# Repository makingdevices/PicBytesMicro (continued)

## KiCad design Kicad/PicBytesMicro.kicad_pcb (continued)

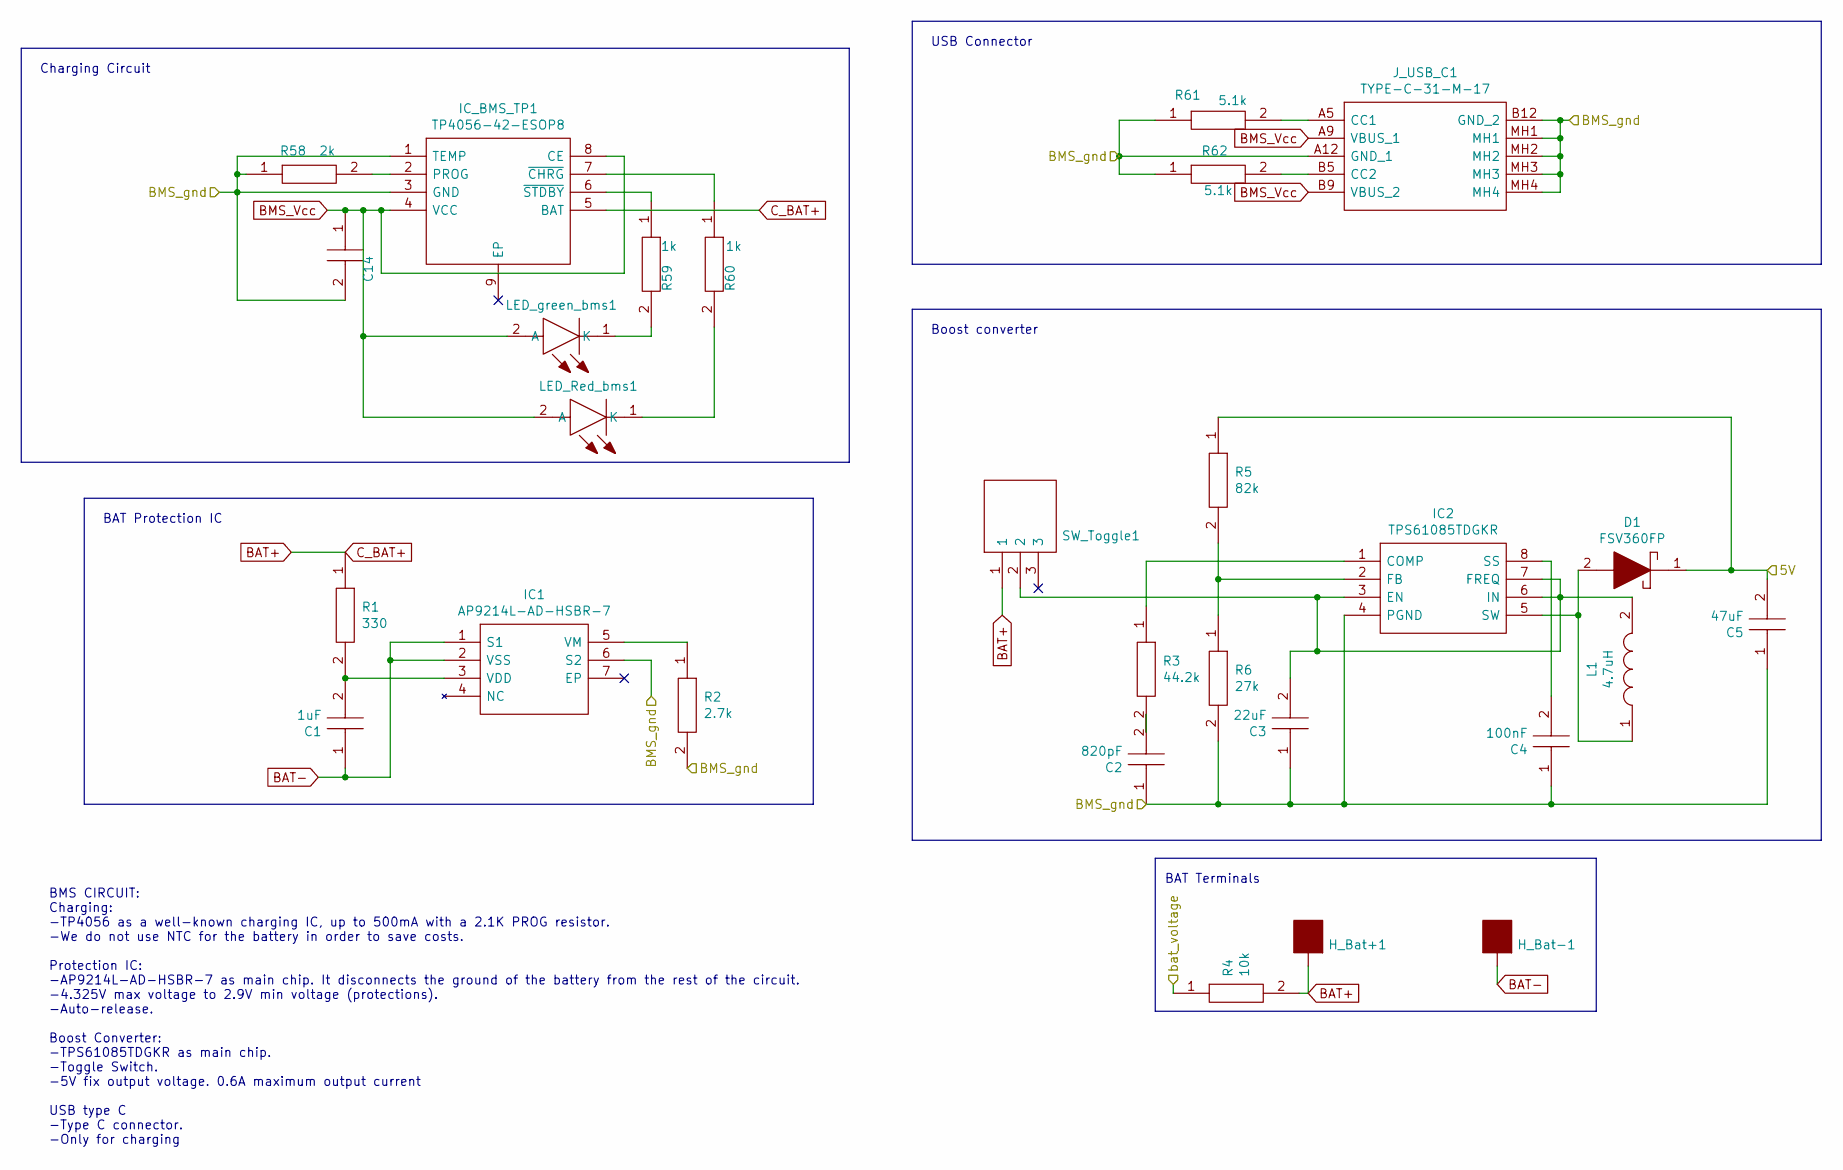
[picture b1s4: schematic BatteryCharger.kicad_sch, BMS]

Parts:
C1: 1uF; CAPC2012X140N; Manufacturer_Part_Number C0805C475M8RACTU
C2: 820pF; CAPC2012X140N; Manufacturer_Part_Number C0805C475M8RACTU
C3: 22uF; CAPC2012X140N; Manufacturer_Part_Number C0805C475M8RACTU
C4: 100nF; CAPC2012X140N; Manufacturer_Part_Number C0805C475M8RACTU
C5: 47uF; CAPC2012X140N; Manufacturer_Part_Number C0805C475M8RACTU
C14: 10uF; CAPC2012X145N; Manufacturer_Part_Number GCG21BR71H154KA01K
D1: FSV360FP; SS12FP; Mouser Part Number 512-FSV360FP
H_Bat+1: MountingHole_Pad-User_library-SamacSys_Parts; Mounting-Pad
H_Bat-1: MountingHole_Pad-User_library-SamacSys_Parts; Mounting-Pad
IC1: AP9214L-AD-HSBR-7; AP9214LANHSBR7; Mouser Part Number 621-AP9214L-AN-HSBR7
IC2: TPS61085TDGKR; SOP65P490X110-8N; Mouser Part Number 595-TPS61085TDGKR
IC_BMS_TP1: TP4056-42-ESOP8; SOIC127P600X175-9N; Manufacturer_Part_Number TP4056-42-ESOP8
J_USB_C1: TYPE-C-31-M-17; TYPEC31M17; Manufacturer_Part_Number TYPE-C-31-M-17
L1: 4.7uH; SRN6045_1; Mouser Part Number 652-SRN6045-4R7Y
LED_Red_bms1: LTST-C171GKT; LEDC2012X90N; Manufacturer_Part_Number LTST-C171GKT
LED_green_bms1: LTST-C171GKT; LEDC2012X90N; Manufacturer_Part_Number LTST-C171GKT
R1: 330; RESC2012X75N; Manufacturer_Part_Number ERJP6WF1303V
R2: 2.7k; RESC2012X75N; Manufacturer_Part_Number ERJP6WF1303V
R3: 44.2k; RESC2012X75N; Manufacturer_Part_Number ERJP6WF1303V
R4: 10k; RESC2012X75N; Manufacturer_Part_Number ERJP6WF1303V
R5: 82k; RESC2012X75N; Manufacturer_Part_Number ERJP6WF1303V
R6: 27k; RESC2012X75N; Manufacturer_Part_Number ERJP6WF1303V
R58: 2k; RESC2012X65N; Manufacturer_Part_Number KTR10EZPF4220
R59, R60: 1k; RESC2012X65N; Manufacturer_Part_Number KTR10EZPF4220
R61, R62: 5.1k; RESC2012X65N; Manufacturer_Part_Number KTR10EZPF4220
SW_Toggle1: K3-1260D-L1; K31260DL1; Manufacturer_Part_Number K3-1260D-L1

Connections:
BAT+: H_Bat+1.1, IC_BMS_TP1.5 (BAT), R1.1, R4.2, SW_Toggle1.1
BAT-: C1.1, H_Bat-1.1, IC1.1 (S1), IC1.2 (VSS)
BMS_Vcc: C14.1, IC_BMS_TP1.4 (VCC), IC_BMS_TP1.8 (CE), J_USB_C1.A9 (VBUS_1), J_USB_C1.B9 (VBUS_2), LED_Red_bms1.2 (A), LED_green_bms1.2 (A)
unnamed: C2.2, R3.2
unnamed: C1.2, IC1.3 (VDD), R1.2
unnamed: IC1.5 (VM), R2.1
unnamed: IC2.1 (COMP), R3.1
unnamed: C3.2, IC2.3 (EN), IC2.6 (IN), IC2.7 (FREQ), L1.2, SW_Toggle1.2
unnamed: IC2.2 (FB), R5.2, R6.1
unnamed: C4.2, IC2.8 (SS)
unnamed: D1.2, IC2.5 (SW), L1.1
unnamed: IC_BMS_TP1.2 (PROG), R58.2
unnamed: IC_BMS_TP1.7 (~CHRG), R60.1
unnamed: IC_BMS_TP1.6 (~STDBY), R59.1
unnamed: J_USB_C1.A5 (CC1), R61.2
unnamed: J_USB_C1.B5 (CC2), R62.2
unnamed: LED_Red_bms1.1 (K), R60.2
unnamed: LED_green_bms1.1 (K), R59.2
Vcc_main: C5.2, D1.1, R5.1; also elsewhere on the board
Vdc_battery: R4.1; also elsewhere on the board
Vgnd_main: C2.1, C3.1, C4.1, C5.1, C14.2, IC1.6 (S2), IC2.4 (PGND), IC_BMS_TP1.1 (TEMP), IC_BMS_TP1.3 (GND), J_USB_C1.A12 (GND_1), J_USB_C1.B12 (GND_2), J_USB_C1.MH1, J_USB_C1.MH2, J_USB_C1.MH3, J_USB_C1.MH4, R2.2, R6.2, R58.1, R61.1, R62.1; also elsewhere on the board

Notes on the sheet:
Boost converter
BMS CIRCUIT: Charging: -TP4056 as a well-known charging IC, up to 500mA with a 2.1K PROG resistor. -We do not use NTC for the battery in order to save costs. Protection IC: -AP9214L-AD-HSBR-7 as main chip. It disconnects the ground of the battery from the rest of the circuit. -4.325V max voltage to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
BAT Protection IC
USB Connector
BAT Terminals
Charging Circuit

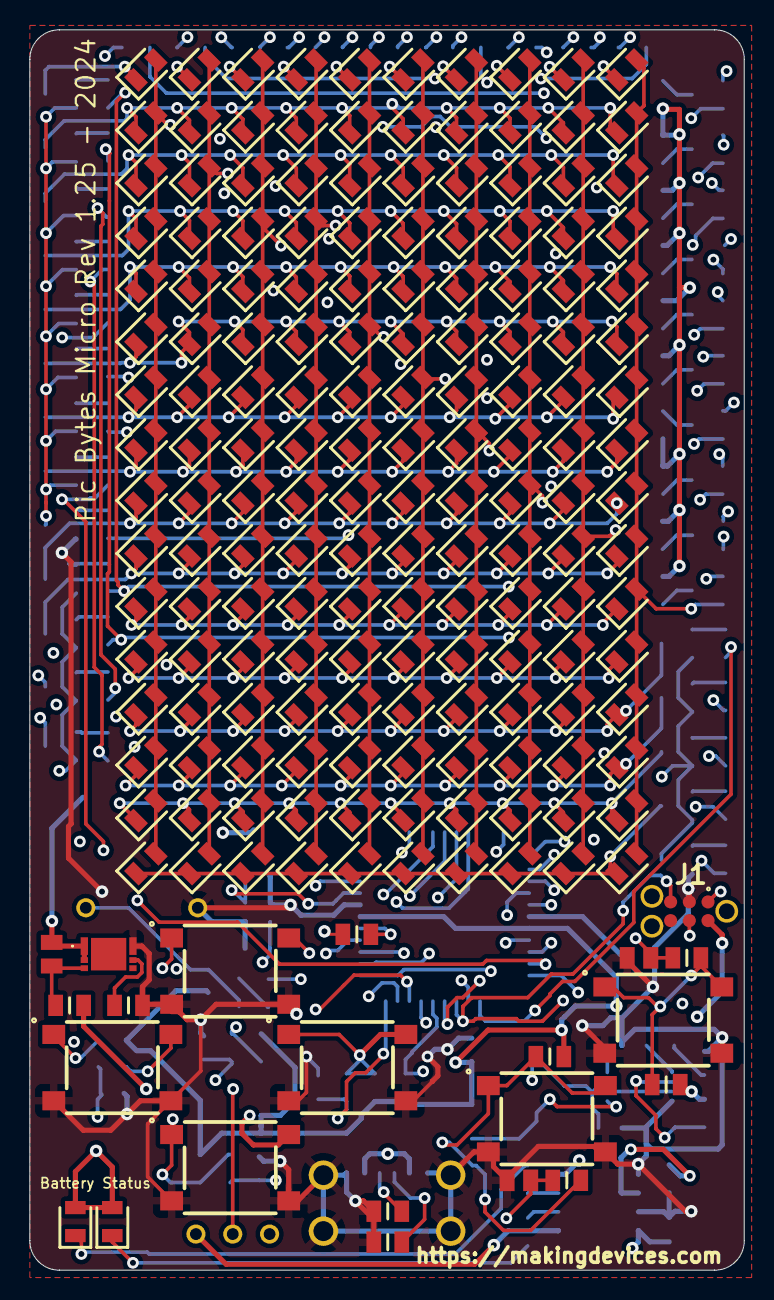
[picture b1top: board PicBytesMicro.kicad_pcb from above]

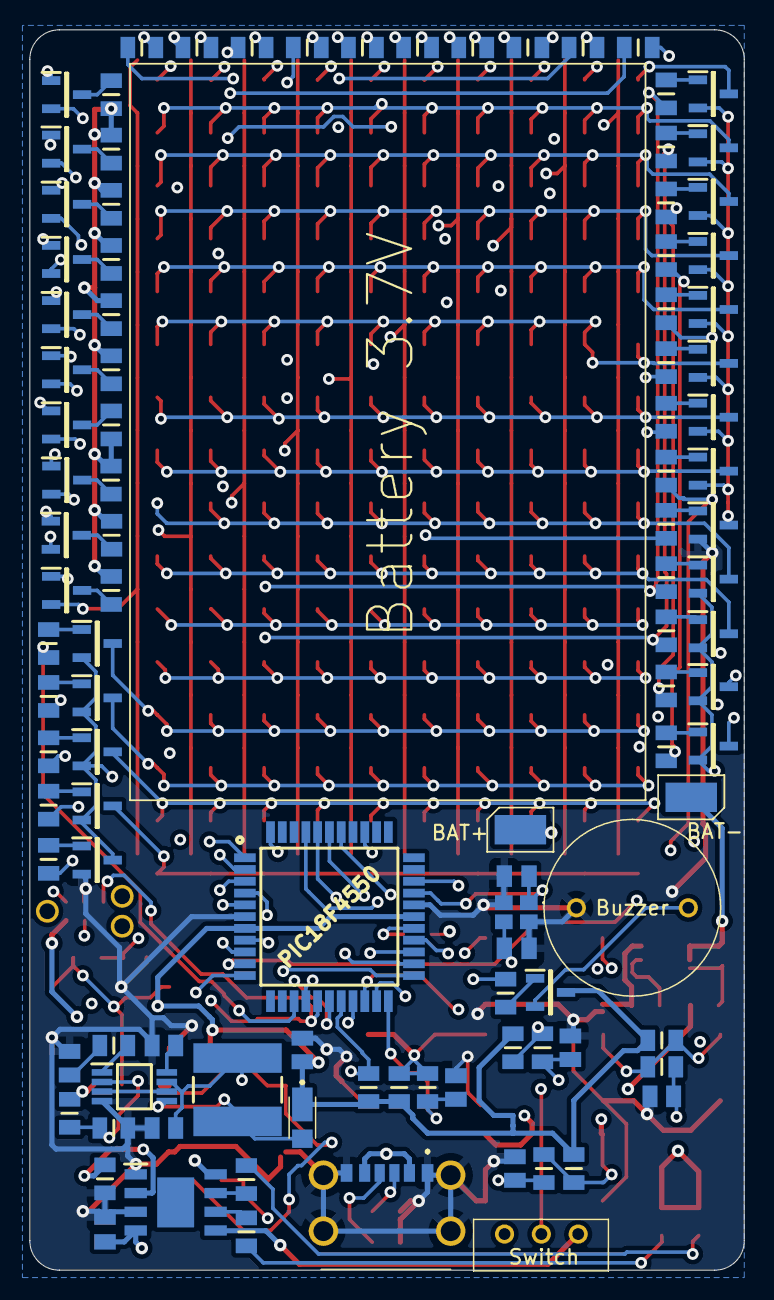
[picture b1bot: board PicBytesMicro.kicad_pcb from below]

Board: 4 copper layers, 48.5 x 84.2 mm, 287 parts (105 on the bottom side), 125 nets.

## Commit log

2023-01-08 Upload files
2023-01-08 no message
2023-06-01 Moving to next version V1.0
2024-01-03 New V1.2 Hardware Release
2024-03-24 V1.25 FW release
2024-03-24 New HW v1.25 release
2024-05-21 New v1.25. Some rescue libs were created as I updated into Kicad 8 with a clean install.
2024-05-22 Updating Readme
2024-05-22 updating readme...
2024-05-23 Small bug fixes
2024-06-04 Finished v1.25 version
2024-06-13 Bill Of Materials
2024-06-27 New fabrication files
2024-09-16 New .hex in case you need to re-install all the memory map on the micro. Wurth Elektronik asked for it :)
